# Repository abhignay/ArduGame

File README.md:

# ArduGame
## About
I first came across the Arduboy when I watched Short Circuit's [video](https://www.youtube.com/watch?v=R6doWcA6q6Y) about the Arduboy Mini, and I was in awe of the super cool device it is. As a fun weekend project, I put together an Arduboy on a protoboard, and after playing on the very janky-looking protoboard for a while, I decided to make a PCB for it which I call the ArduGame.

## Hardware
The ArduGame uses an Arduino Pro Micro as its microcontroller, and an SH1106 1.3" SPI OLED as its screen. Additionally, there's a TP4056 LiPo manager along with a 3.3V to 5V step-up converter (MT3608). I've designed the ArduGame to be powered by a 3.3V LiPo battery

## Software
To be able to upload game files (in the .ino file format) download MrBlinky's [Arduboy-homemade-package](https://github.com/MrBlinky/Arduboy-homemade-package) and upload your favorite game!

If you have any questions, comments or suggestions open up an issue!

## License

Code in this repository is licensed under the terms of the MIT license.

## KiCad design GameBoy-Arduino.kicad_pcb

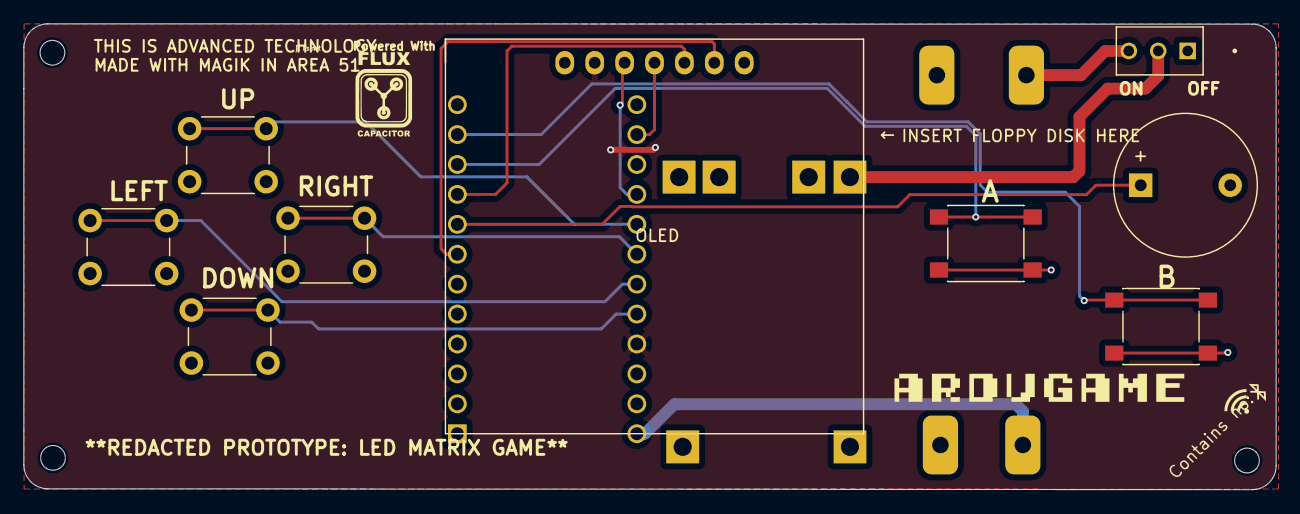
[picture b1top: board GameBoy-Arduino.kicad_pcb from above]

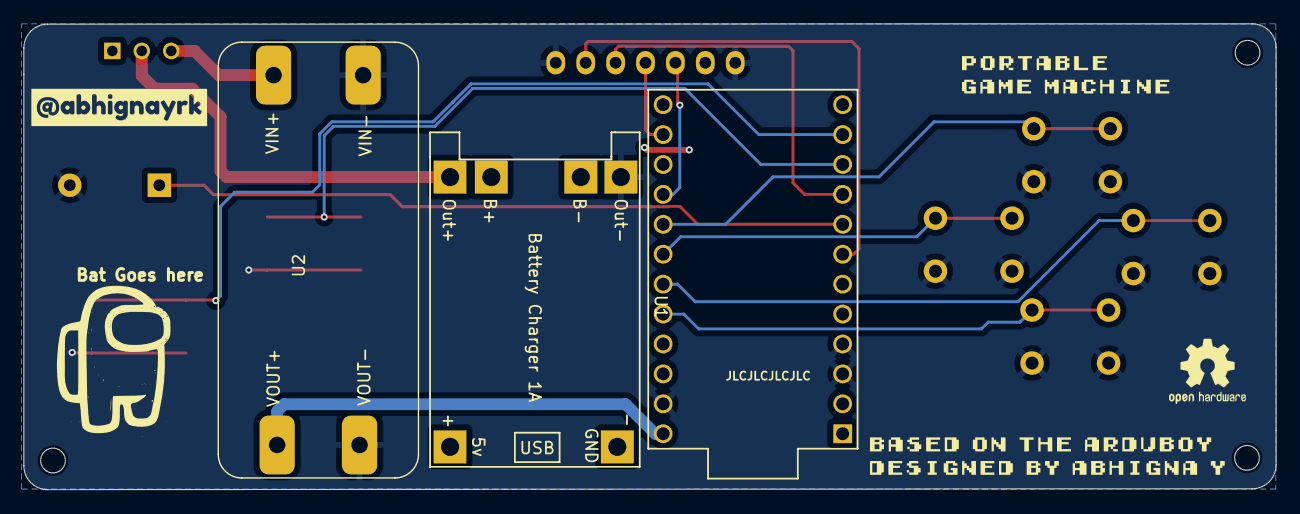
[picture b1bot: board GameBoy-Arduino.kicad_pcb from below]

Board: 2 copper layers, 106.3 x 39.5 mm, 16 parts (6 on the bottom side), 16 nets.

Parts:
BZ1: Buzzer; Buzzer_12x9.5RM7.6
SW1, SW2, SW3, SW4: SW_Push_Open; SW_PUSH_6mm_H5mm
SW5, SW6: SW_Push_Open; SW_Push_1P1T_NO_6x6mm_H9.5mm
SW7: SW_SPDT; SW_MINI-SPDT-SW
U1: TP4056; TP4056-18650
U2: MT3608; MT3608-Module
U4: Arduino Pro Micro; ProMicro-EnforcedTop
U5: SH1106
kibuzzard-653BC246: G***; kibuzzard-653BC246
kibuzzard-65312D56: G***; kibuzzard-65312D56
kibuzzard-65549CA5: G***; kibuzzard-65549CA5
kibuzzard-653130E3: G***; kibuzzard-653130E3

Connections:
+3.3V: U4.21 (VCC), U5.2 (VCC)
+5V: U2.3 (VOUT+), U4.24 (RAW)
/BOOST_OUT: SW7.3 (C), U2.1 (VIN+)
/Buttons/BTNA: SW5.1 (A), U4.10 (D7)
/Buttons/BTNB: SW6.1 (A), U4.11 (D8)
/Buttons/BTNDWN: SW2.1 (A), U4.20 (A3)
/Buttons/BTNLFT: SW3.1 (A), U4.18 (A1)
/Buttons/BTNRIGHT: SW4.1 (A), U4.19 (A2)
/Buttons/BTNUP: SW1.1 (A), U4.17 (A0)
/LCD/CLK: U4.16 (D15), U5.3 (CLK)
/LCD/DC: U4.7 (D4), U5.6 (DC)
/LCD/MOSI: U4.14 (D16), U5.4 (MOSI)
/LCD/RES: U4.9 (D6), U5.5 (RES)
/LiManage_OUT: SW7.2 (B), U1.3 (OUT+)
/Microcontroller/Buzzer: BZ1.1 (-), U4.8 (D5)
GND: BZ1.2 (+), SW1.2 (B), SW2.2 (B), SW3.2 (B), SW4.2 (B), SW5.2 (B), SW6.2 (B), U1.4 (OUT-), U2.2 (VIN-), U2.4 (VOUT-), U4.3 (GND), U4.4 (GND), U4.23 (GND), U5.1 (GND), U5.7 (CS)

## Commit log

2024-05-04 updated photo
2024-05-06 updated silkscreen
